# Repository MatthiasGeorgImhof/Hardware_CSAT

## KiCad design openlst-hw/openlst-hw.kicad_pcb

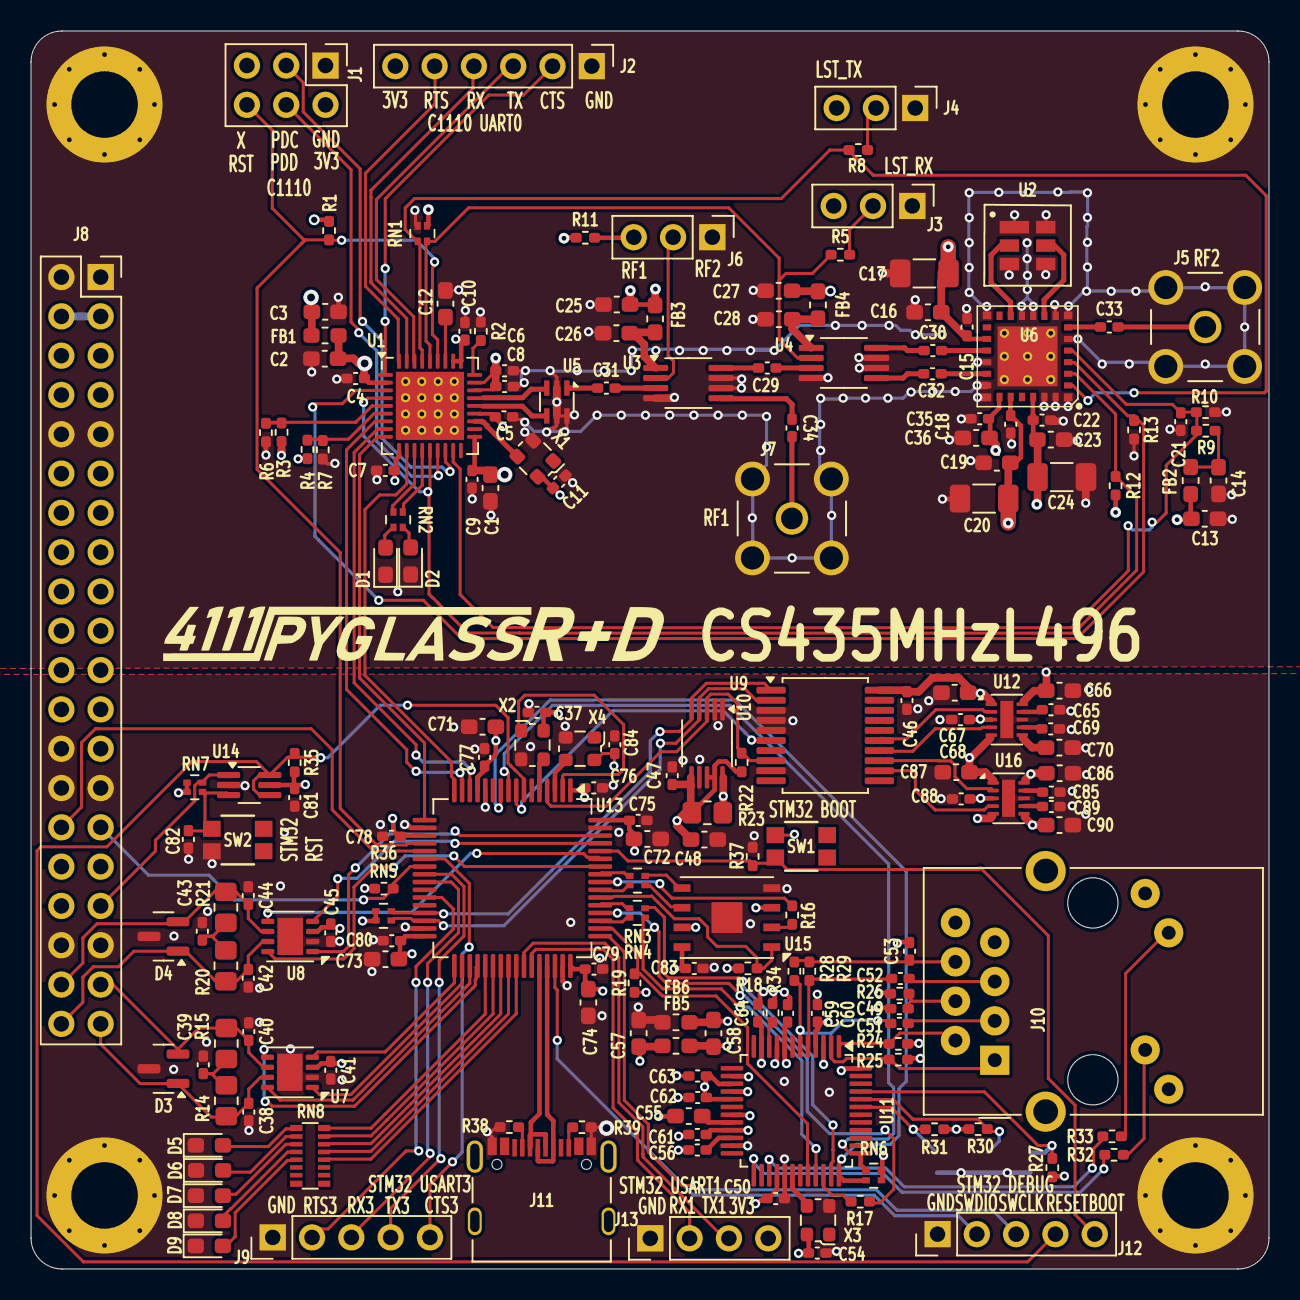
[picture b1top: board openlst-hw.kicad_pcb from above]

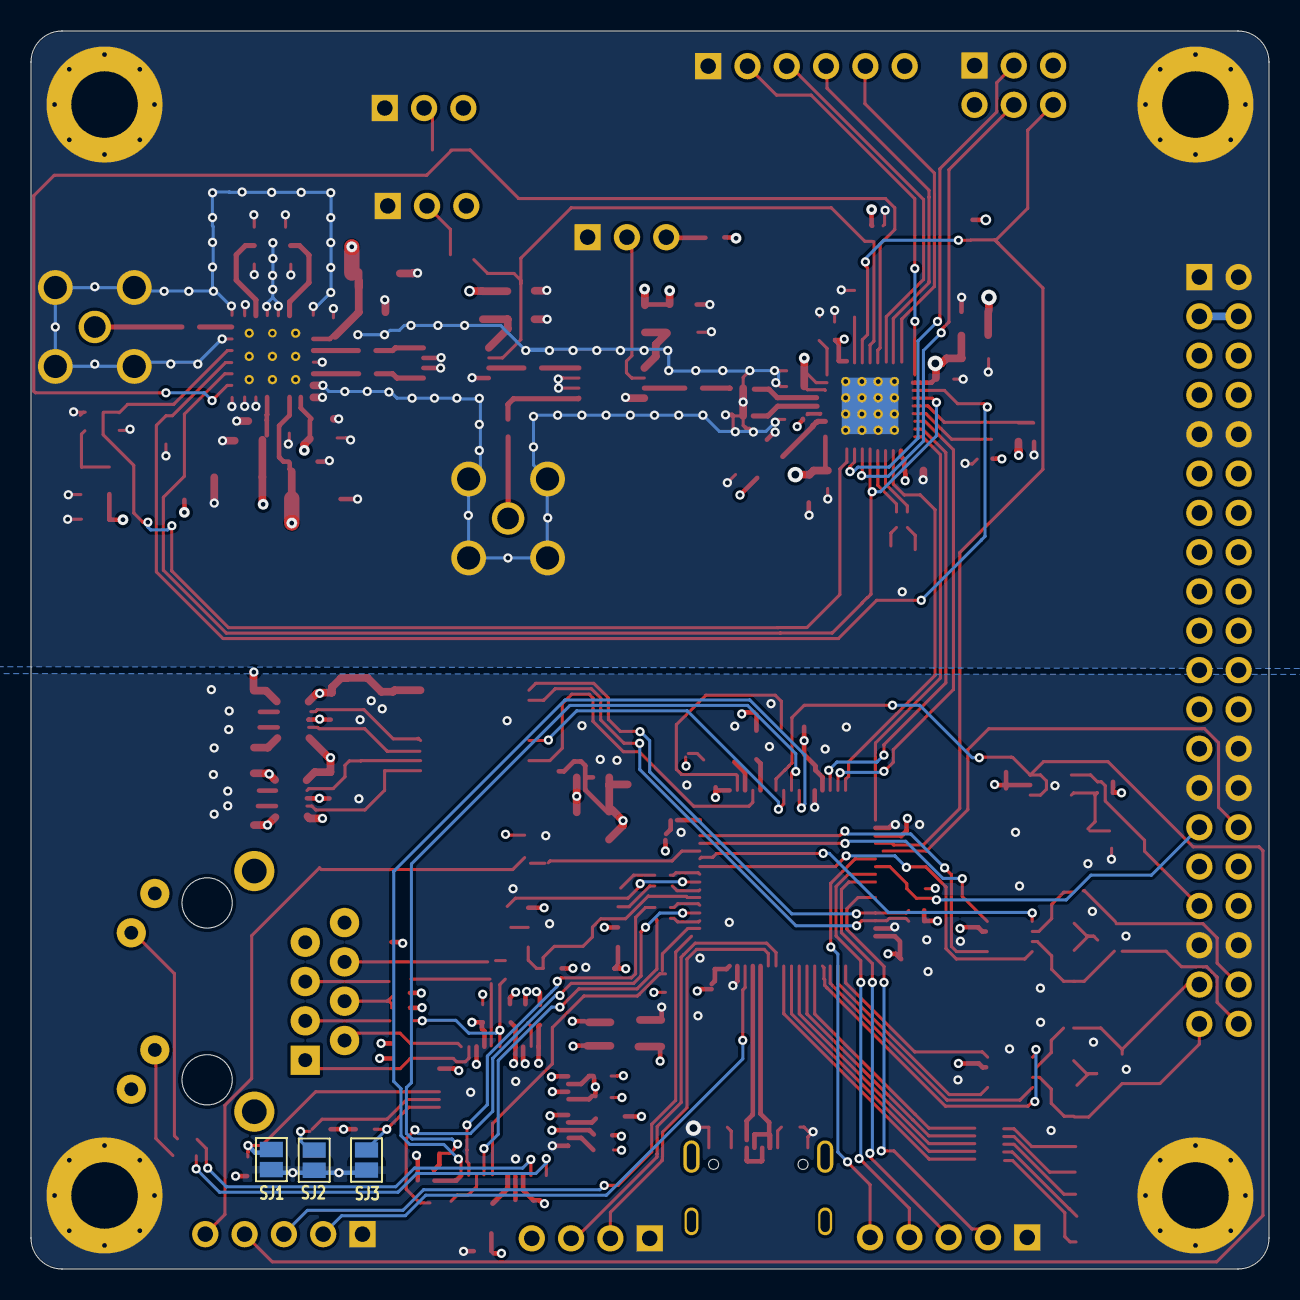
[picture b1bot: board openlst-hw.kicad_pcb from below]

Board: 4 copper layers, 80.0 x 80.0 mm, 194 parts (3 on the bottom side), 153 nets.

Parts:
C1, C16, C19, C23, C36, C48, C55, C57, C58, C66, C70, C71, C72, C73, C74, C86, C90: 10uF; C_0603_1608Metric_Pad1.08x0.95mm_HandSolder
C2, C3, C12, C13, C14, C25, C26, C27, C28: 1uF; C_0603_1608Metric_Pad1.08x0.95mm_HandSolder
C4, C5, C6, C7, C8, C9, C10, C11, C15, C18, C21, C22, C35, C37, C41, C45, C46, C47, C50, C54, C56, C59, C60, C61, C62, C63, C64, C68, C75, C76, C77, C78, C79, C80, C81, C82, C83, C84, C88: 100nF; C_0402_1005Metric_Pad0.74x0.62mm_HandSolder
C17, C20, C24: 47uF; C_1206_3216Metric_Pad1.33x1.80mm_HandSolder
C29, C30, C31, C32, C33, C34, C65, C69, C85, C89: 220pF; C_0402_1005Metric_Pad0.74x0.62mm_HandSolder
C38, C40, C42, C44: 100pF; C_0402_1005Metric_Pad0.74x0.62mm_HandSolder
C39, C43: 4nF7; C_0402_1005Metric_Pad0.74x0.62mm_HandSolder
C49, C53: 10nF; C_0402_1005Metric_Pad0.74x0.62mm_HandSolder
C51, C52: 6.8nF; C_0402_1005Metric_Pad0.74x0.62mm_HandSolder
C67, C87: 22uF; C_0603_1608Metric_Pad1.08x0.95mm_HandSolder
D1, D6: GREEN; LED_0603_1608Metric_Pad1.05x0.95mm_HandSolder
D2, D7, D8, D9: YELLOW; LED_0603_1608Metric_Pad1.05x0.95mm_HandSolder
D3, D4: NUP2105LT1G; SOT-23
D5: RED; LED_0603_1608Metric_Pad1.05x0.95mm_HandSolder
FB1, FB2, FB3, FB4, FB5, FB6: 1K; L_0603_1608Metric_Pad1.05x0.95mm_HandSolder
H1, H2, H3, H4: MountingHole_Pad; MountingHole_4.3mm_M4_Pad_Via_Custom
J1: Conn_02x03_Pin; PinHeader_2x03_P2.54mm_Vertical
J2: Conn_01x06_Pin; PinHeader_1x06_P2.54mm_Vertical
J3, J4, J6: Conn_01x03_Pin; PinHeader_1x03_P2.54mm_Vertical
J5, J7: SMA Jack; LINX_CONSMA001-G
J8: PC104 Conn_02x20_Odd_Even; PinSocket_2x20_P2.54mm_Vertical
J9: Conn_01x05_Pin; PinHeader_1x05_P2.54mm_Vertical
J10: RJ45_Amphenol_RJMG1BD3B8K1ANR
J11: 10155435-00011LF; AMPHENOL_10155435-00011LF
J12: Conn_01x05_Pin Vertical; PinHeader_1x05_P2.54mm_Vertical
J13: Conn_01x04_Pin Vertical; PinHeader_1x04_P2.54mm_Vertical
R1, R18, R19, R22, R35, R37: 100K; R_0402_1005Metric_Pad0.72x0.64mm_HandSolder
R2: 56K; R_0402_1005Metric_Pad0.72x0.64mm_HandSolder
R3, R4, R11: 20K; R_0402_1005Metric_Pad0.72x0.64mm_HandSolder
R5, R8: 22; R_0402_1005Metric_Pad0.72x0.64mm_HandSolder
R6, R7: 47K; R_0402_1005Metric_Pad0.72x0.64mm_HandSolder
R9: 3K09; R_0402_1005Metric_Pad0.72x0.64mm_HandSolder
R10: 6K65; R_0402_1005Metric_Pad0.72x0.64mm_HandSolder
R12, R13: 1K; R_0402_1005Metric_Pad0.72x0.64mm_HandSolder
R14, R15, R20, R21: 60R4; R_0805_2012Metric_Pad1.20x1.40mm_HandSolder
R16, R17: 22R; R_0402_1005Metric_Pad0.72x0.64mm_HandSolder
R23: 10m; R_0805_2012Metric_Pad1.20x1.40mm_HandSolder
R24, R25, R28, R29: 49R9; R_0402_1005Metric_Pad0.72x0.64mm_HandSolder
R26: 10R; R_0402_1005Metric_Pad0.72x0.64mm_HandSolder
R27, R30, R31: 10K; R_0402_1005Metric_Pad0.72x0.64mm_HandSolder
R32, R33: 470R; R_0402_1005Metric_Pad0.72x0.64mm_HandSolder
R34: 12K4; R_0402_1005Metric_Pad0.72x0.64mm_HandSolder
R36: 330K; R_0402_1005Metric_Pad0.72x0.64mm_HandSolder
R38, R39: 5K1; R_0402_1005Metric_Pad0.72x0.64mm_HandSolder
RN1, RN6: 10K; R_Array_Convex_2x0402_widepads
RN2: 1K; R_Array_Convex_2x0402_widepads
RN3, RN4: 22R; R_Array_Convex_2x0402_widepads
RN5: 5K6; R_Array_Convex_2x0402_widepads
RN7: 100K; R_Array_Convex_2x0402_widepads
RN8: 1K; R_Array_Convex_8x0602_widepads
SJ1, SJ2, SJ3: SOLDERJUMPERREFLOW_NOPASTE; SolderJumper-2_P1.3mm_Open_Pad1.0x1.5mm
SW1, SW2: EVP-AA602W; EVP602AA
U1: CC1110; Texas_RHH0036C_VQFN-36-1EP_6x6mm_P0.5mm_EP4.4x4.4mm_Thermal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
U2: TA1808A; SF2446E
U3, U4: PE4250MLI; MSOP-8_3x3mm_P0.65mm
U5: 0433BM15A0001; Balun_Johanson_0896BM15A0001
U6: RFFM6406
U7, U8: TCAN3414; VSON-8-1EP_3x3mm_P0.65mm_EP1.65x2.4mm
U9: MCP23008T-E/SS; SSOP-20_5.3x7.2mm_P0.65mm
U10: INA226AIDGSR; VSSOP-10_3x3mm_P0.5mm
U11: W5500; LQFP-48_7x7mm_P0.5mm
U12, U16: TPS22968QDMGRQ1; WSON-10-1EP_2x3mm_P0.5mm_EP0.84x2.4mm
U13: STM32L496RGTx; LQFP-64_10x10mm_P0.5mm
U14: 74LVC2G07; SOT-363_SC-70-6_Handsoldering
U15: MR25H10; DFN-8-1EP_6x5mm_P1.27mm_EP2x2mm
X1: 27MHz; Oscillator_SMD_ECS_2520MV-xxx-xx-4Pin_2.5x2.0mm
X2: 10MHz; Oscillator_SMD_ECS_2520MV-xxx-xx-4Pin_2.5x2.0mm
X3: 25MHz; Oscillator_SMD_ECS_2520MV-xxx-xx-4Pin_2.5x2.0mm
X4: 32.768KHZ; Oscillator_SMD_ECS_2520MV-xxx-xx-4Pin_2.5x2.0mm

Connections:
/3V3_AUX: J8.15, R23.1, U10.10 (IN+)
/3V3_BRIDGE: C37.1, C41.1, C45.1, C71.1, C72.1, C73.1, C74.1, C75.1, C76.1, C77.1, C78.1, C79.1, C80.1, C81.2, C84.1, J8.16, J13.4, R35.1, R36.1, RN5.3 (R2.2), RN5.4 (R1.2), RN7.1 (R1.1), RN7.2 (R2.1), SW1.1, U7.3 (VCC), U8.3 (VCC), U13.1 (VBAT), U13.13 (VDDA), U13.19 (VDD), U13.32 (VDD), U13.48 (VDDUSB), U13.64 (VDD), U14.5 (VCC), X2.4 (VDD), X4.4 (VCC)
/3V3_COMM: C3.1, C11.1, C13.1, C25.1, C27.1, C35.1, C36.1, C66.1, FB1.1, FB2.2, FB3.2, FB4.2, J1.2, J2.6, J3.3, J4.3, R1.2, R3.2, R11.1, R12.2, RN1.3 (R2.2), U6.23 (VDD), U12.10 (VOUT1), X1.4 (Vcc)
/3V3_LAN: C50.1, C54.1, C57.1, C90.2, FB5.1, J10.L1, J10.L4, R19.1, R27.1, R30.1, R31.1, RN6.3 (R2.2), RN6.4 (R1.2), U11.28 (VDD), U16.6 (VOUT2), X3.4 (VCC)
/CAN Bridge/3V3_MRAM: C83.1, C86.1, R18.1, U15.3 (~WP), U15.7 (~HOLD), U15.8 (VDD), U16.10 (VOUT1)
/CAN Bridge/ATTENTION: J8.29, R36.2, U13.23 (PA7)
/CAN Bridge/CAN1_H: C42.1, D4.1 (K), J8.40, R20.1, U8.7 (CANH)
/CAN Bridge/CAN1_L: C44.2, D4.2 (K), J8.38, R21.2, U8.6 (CANL)
/CAN Bridge/CAN2_H: C38.1, D3.1 (K), J8.39, R14.1, U7.7 (CANH)
/CAN Bridge/CAN2_L: C40.2, D3.2 (K), J8.37, R15.2, U7.6 (CANL)
/CAN Bridge/CAN Transceiver1/CAN_RX: U8.4 (RXD), U13.61 (PB8)
/CAN Bridge/CAN Transceiver1/CAN_TX: U8.1 (TXD), U13.62 (PB9)
/CAN Bridge/CAN Transceiver1/SHDN: U8.5 (SHTD), U13.59 (PB7)
/CAN Bridge/CAN Transceiver1/STB: U8.8 (STB), U13.58 (PB6)
/CAN Bridge/CAN Transceiver2/CAN_RX: U7.4 (RXD), U13.33 (PB12)
/CAN Bridge/CAN Transceiver2/CAN_TX: U7.1 (TXD), U13.34 (PB13)
/CAN Bridge/CAN Transceiver2/SHDN: U7.5 (SHTD), U13.36 (PB15)
/CAN Bridge/CAN Transceiver2/STB: U7.8 (STB), U13.35 (PB14)
/CAN Bridge/COMM1_RST: J8.33, RN7.4 (R1.2), U14.1 (IN1)
/CAN Bridge/EPS_RST: J8.30, U13.21 (PA5)
/CAN Bridge/I2C2_SCL: RN5.2 (R2.1), U9.1 (SCL), U10.5 (SCL), U13.29 (PB10)
/CAN Bridge/I2C2_SDA: RN5.1 (R1.1), U9.2 (SDA), U10.4 (SDA), U13.30 (PB11)
/CAN Bridge/MRAM/SPI_MISO: R16.1, U15.2 (SO)
/CAN Bridge/MRAM/SPI_MOSI: RN3.2 (R2.1), U15.5 (SI)
/CAN Bridge/MRAM/SPI_SCK: RN3.1 (R1.1), U15.6 (SCK)
/CAN Bridge/PMIC/BOOT: J12.5, R37.1, SW1.2, U13.60 (PH3_BOOT0)
/CAN Bridge/PMIC/EXTI2_LAN: RN6.2 (R2.1), U11.36 (~INT), U13.10 (PC2)
/CAN Bridge/PMIC/HSE_EN: U13.2 (PC13), X2.1 (TRI-STATE)
/CAN Bridge/PMIC/HSE_IN: U13.5 (PH0), X2.3 (OUTPUT)
/CAN Bridge/PMIC/LAN_RST: RN6.1 (R1.1), U11.37 (~RST), U13.9 (PC1)
/CAN Bridge/PMIC/LED1: RN8.16 (R), U13.37 (PC6)
/CAN Bridge/PMIC/LED2: RN8.15 (R), U13.38 (PC7)
/CAN Bridge/PMIC/LED3: RN8.14 (R), U13.39 (PC8)
/CAN Bridge/PMIC/LED4: RN8.13 (R), U13.40 (PC9)
/CAN Bridge/PMIC/LED5: RN8.12 (R), U13.41 (PA8)
/CAN Bridge/PMIC/NRST: J12.4, R35.2, U13.7 (NRST), U14.4 (OUT2), U14.6 (OUT1)
/CAN Bridge/PMIC/OSC32_IN: U13.3 (PC14), X4.3 (OUT)
/CAN Bridge/PMIC/RESET: C82.1, RN7.3 (R2.2), SW2.3, U14.3 (IN2)
/CAN Bridge/PMIC/SPI1_MISO: R16.2, U13.56 (PB4)
/CAN Bridge/PMIC/SPI1_MOSI: RN3.3 (R2.2), U13.57 (PB5)
/CAN Bridge/PMIC/SPI1_SCK: RN3.4 (R1.2), U13.55 (PB3)
/CAN Bridge/PMIC/SPI3_MISO: R17.1, U13.52 (PC11)
/CAN Bridge/PMIC/SPI3_MOSI: RN4.3 (R2.2), U13.53 (PC12)
/CAN Bridge/PMIC/SPI3_SCK: RN4.4 (R1.2), U13.51 (PC10)
/CAN Bridge/PMIC/SYS_JTMS_SWCLK: J12.3, U13.49 (PA14)
/CAN Bridge/PMIC/SYS_JTMS_SWDIO: J12.2, U13.46 (PA13)
/CAN Bridge/PMIC/USART1_RX: J13.2, U13.43 (PA10)
/CAN Bridge/PMIC/USART1_TX: J13.3, U13.42 (PA9)
/CAN Bridge/PMIC/USART3_CTS: J9.5, U13.22 (PA6)
/CAN Bridge/PMIC/USART3_RTS: J9.2, U13.27 (PB1)
/CAN Bridge/PMIC/USART3_RX: J9.3, U13.25 (PC5)
/CAN Bridge/PMIC/USART3_TX: J9.4, U13.24 (PC4)
/CAN Bridge/PMIC/USB/DN: J11.A7 (DN1_A), J11.B7 (DN2_B), U13.44 (PA11)
/CAN Bridge/PMIC/USB/DP: J11.A6 (DP1_A), J11.B6 (DP2_B), U13.45 (PA12)
/CAN Bridge/Power Switch/ENABLE0: U9.12 (GP0), U16.4 (ON2)
/CAN Bridge/Power Switch/ENABLE1: U9.13 (GP1), U16.2 (ON1)
/CAN Bridge/Power Switch/ENABLE2: U9.14 (GP2), U12.4 (ON2)
/CAN Bridge/Power Switch/ENABLE3: U9.15 (GP3), U12.2 (ON1)
/CAN Bridge/Power Switch/VBUS: C46.1, C47.1, C48.1, C67.1, C68.1, C87.1, C88.1, R22.1, R23.2, U9.20 (VDD), U10.6 (VS), U10.8 (VBUS), U10.9 (IN-), U12.1 (VIN1), U12.3 (VBIAS), U12.5 (VIN2), U16.1 (VIN1), U16.3 (VBIAS), U16.5 (VIN2)
/CAN Bridge/Power Switch/VOUT2: C70.2, U12.6 (VOUT2)
/CAN Bridge/Power_INT: R22.2, U9.8 (INT), U10.3 (ALERT), U13.4 (PC15)
/CAN Bridge/Power_RST: U9.6 (*RESET), U13.8 (PC0)
/CAN Bridge/SPI1_CS_LAN: R19.2, U11.32 (~SCS), U13.50 (PA15)
/CAN Bridge/SPI1_CS_MRAM: R18.2, U13.54 (PD2), U15.1 (~CS)
/CAN Bridge/SPI_LAN/AGND: C49.2, C53.2, C55.2, C56.2, C58.2, C59.2, C60.2, C61.2, C62.2, C63.2, C64.2, FB6.2, J10.R8, R34.2, U11.3 (AGND), U11.9 (AGND), U11.14 (AGND), U11.16 (AGND), U11.19 (AGND), U11.48 (AGND)
/CAN Bridge/SPI_LAN/AVDD: C58.1, C59.1, C60.1, C61.1, C62.1, C63.1, C64.1, FB5.2, R24.1, R25.1, R26.1, U11.4 (AVDD), U11.8 (AVDD), U11.11 (AVDD), U11.15 (AVDD), U11.17 (AVDD), U11.21 (AVDD)
/CAN Bridge/SPI_LAN/GREENLED: J10.L3, R32.1
/CAN Bridge/SPI_LAN/MISO: R17.2, U11.34 (MISO)
/CAN Bridge/SPI_LAN/MOSI: RN4.2 (R2.1), U11.35 (MOSI)
/CAN Bridge/SPI_LAN/RX+: C51.2, R28.2, U11.6 (RXP)
/CAN Bridge/SPI_LAN/RX-: C52.2, R29.2, U11.5 (RXN)
/CAN Bridge/SPI_LAN/SCKL: RN4.1 (R1.1), U11.33 (SCLK)
/CAN Bridge/SPI_LAN/TX+: J10.R1 (TD+), R25.2, U11.2 (TXP)
/CAN Bridge/SPI_LAN/TX-: J10.R2 (TD-), R24.2, U11.1 (TXN)
/CAN Bridge/SPI_LAN/YELLOWLED: J10.L2, R33.1
/CAN Bridge/UART_CTS: U1.8 (P0_3), U13.14 (PA0)
/CAN Bridge/UART_RTS: U1.7 (P0_2), U13.15 (PA1)
/CAN Bridge/UART_RX: U1.9 (P0_4), U13.17 (PA3)
/CAN Bridge/UART_TX: U1.11 (P0_5), U13.16 (PA2)
/GND: C1.2, C2.2, C3.2, C4.2, C5.2, C6.2, C7.2, C8.2, C9.2, C10.2, C11.2, C12.2, C13.2, C14.2, C15.2, C16.2, C17.2, C18.2, C19.2, C20.2, C21.2, C22.2, C23.2, C24.2, C25.2, C26.2, C27.2, C28.2, C35.2, C36.2, C37.2, C38.2, C39.2, C40.1, C41.2, C42.2, C43.2, C44.1, C45.2, C46.2, C47.2, C48.2, C50.2, C54.2, C57.2, C65.2, C66.2, C67.2, C68.2, C69.1, C70.1, C71.2, C72.2, C73.2, C74.2, C75.2, C76.2, C77.2, C78.2, C79.2, C80.2, C81.1, C82.2, C83.2, C84.2, C85.2, C86.2, C87.2, C88.2, C89.1, C90.1, D1.1 (K), D2.1 (K), D3.3 (A), D4.3 (A), D5.1 (K), D6.1 (K), D7.1 (K), D8.1 (K), D9.1 (K), FB6.1, H1.1, H2.1, H3.1, H4.1, J1.1, J2.1, J3.1, J4.1, J5.2 (Ext), J6.1, J7.2 (Ext), J8.1, J8.2, J8.9, J8.10, J8.26, J8.27, J8.28, J8.35, J8.36, J9.1, J11.A1_B12 (GND), J11.B1_A12 (GND__1), J12.1, J13.1, R2.1, R6.1, R7.1, R10.2, R13.1, R37.2, R38.1, R39.1, RN1.4 (R1.2), SJ1.2 (B), SJ2.2 (B), SJ3.2 (B), SW2.4, U1.37 (GND_PAD), U2.1 (GND), U2.3 (GND), U2.4 (GND), U2.6 (GND), U3.4 (GND), U3.6 (GND), U3.7 (GND), U4.4 (GND), U4.6 (GND), U4.7 (GND), U5.2 (GND), U5.5 (GND), U5.6 (GND), U6.1 (GND), U6.6 (GND), U6.8 (GND), U6.9 (GND), U6.11 (GND), U6.12 (GND), U6.15 (GND), U6.19 (GND), U6.21 (GND), U6.22 (GND), U6.27 (GND), U6.28 (GND), U6.29 (PAD), U7.2 (GND), U7.9 (GND), U8.2 (GND), U8.9 (GND), U9.3 (A2), U9.4 (A1), U9.5 (A0), U9.9 (VSS), U10.1 (A1), U10.2 (A0), U10.7 (GND), U11.23 (RSVD), U11.29 (GND), U12.8 (GND), U12.11 (TPAD), U13.12 (VSSA), U13.18 (VSS), U13.31 (VSS), U13.47 (VSS), U13.63 (VSS), U14.2 (GND), U15.4 (VSS), U15.9 (PAD), U16.8 (GND), U16.11 (TPAD), X1.2 (GND), X2.2 (GND), X3.2 (GND), X4.2 (GND)
/INTERBOARD_CONNECTOR2/BATT: J8.3, J8.4
/MCU/+3V3_C1110: C1.1, C2.1, C4.1, C5.1, C6.1, C7.1, C8.1, C9.1, C10.1, FB1.2, U1.2 (DVDD), U1.10 (DVDD), U1.19 (AVDD), U1.22 (AVDD), U1.25 (AVDD), U1.26 (AVDD), U1.28 (GUARD), U1.29 (AVDD_DREG)
/MCU/AN0: R3.1, R6.2, U1.5 (P0_0)
/MCU/AN1: R4.1, R7.2, U1.6 (P0_1)
/MCU/LED1: RN2.2 (R2.1), U1.12 (P0_6)
/MCU/LED2: RN2.1 (R1.1), U1.13 (P0_7)
/MCU/LST_RX_MODE: R5.1, RN1.2 (R2.1), U1.32 (P1_7), U4.2 (V1)
/MCU/LST_TX_MODE: R8.1, RN1.1 (R1.1), U1.33 (P1_6), U6.2 (TR)
/MCU/PA_VAPC: C21.1, R9.2, R10.1, U1.17 (P2_3/XOSC32-1), U6.5 (VAPC)
/MCU/RF_BYP: R13.2, U1.3 (P1_1), U6.4 (BYP)
/MCU/RF_EN: R12.1, U1.4 (P1_0), U1.14 (P2_0), U6.3 (EN)
/MCU/RF_N: U1.24 (RF_N), U5.3
/MCU/RF_P: U1.23 (RF_P), U5.4
/MCU/UART0_CTS: J2.2, U1.1 (P1_2)
/MCU/UART0_RTS: J2.5, U1.36 (P1_3)
/MCU/UART0_RX: J2.4, U1.35 (P1_4)
/MCU/UART0_TX: J2.3, U1.34 (P1_5)
/VRF: C15.1, C16.1, C17.1, C18.1, C19.1, C20.1, C22.1, C23.1, C24.1, J8.5, R4.2, U6.17 (VCC_RX), U6.24 (VCC_TX1), U6.26 (VCC_TX2)
LST_RESET: J1.6, R1.1, U1.31 (RESET_N), U13.20 (PA4)
unnamed: C14.1, FB2.1, R9.1
unnamed: C31.1, U5.1
unnamed: C39.1, R14.2, R15.1
unnamed: C43.1, R20.2, R21.1
unnamed: D1.2 (A), RN2.3 (R2.2)
unnamed: D2.2 (A), RN2.4 (R1.2)
unnamed: D5.2 (A), RN8.1 (R)
unnamed: D6.2 (A), RN8.2 (R)
unnamed: D7.2 (A), RN8.3 (R)
unnamed: D8.2 (A), RN8.4 (R)
unnamed: D9.2 (A), RN8.5 (R)
unnamed: J3.2, R5.2
unnamed: J4.2, R8.2
unnamed: C33.2, J5.1 (In)
unnamed: J6.2, U3.2 (V1)
unnamed: J6.3, R11.2
unnamed: C34.2, J7.1 (In)
unnamed: C52.1, J10.R5 (RCT)
unnamed: C51.1, J10.R3 (RD+)
unnamed: C53.1, J10.R6 (RD-), R28.1, R29.1
unnamed: C49.1, J10.R4 (TCT), R26.2
unnamed: J11.A5 (CC1_A), R38.2
unnamed: J11.B5 (CC2_B), R39.2
unnamed: R27.2, SJ1.1 (A), U11.45 (PMODE0)
unnamed: R30.2, SJ2.1 (A), U11.44 (PMODE1)
unnamed: R31.2, SJ3.1 (A), U11.43 (PMODE2)
unnamed: C12.1, U1.30 (DCOUPL)
unnamed: R2.2, U1.27 (RBIAS)
unnamed: U1.21 (XOSC-1), X1.3 (OUT)
unnamed: C34.1, U3.5 (RF1)
unnamed: C29.1, U3.8 (RF2)
unnamed: C31.2, U3.3 (RFC)
unnamed: C26.1, FB3.1, U3.1 (V2)
unnamed: C32.1, U4.5 (RF1)
unnamed: C30.1, U4.8 (RF2)
unnamed: C29.2, U4.3 (RFC)
unnamed: C28.1, FB4.1, U4.1 (V2)
unnamed: C33.1, U6.7 (ANT)
unnamed: C30.2, U6.18 (RX)
unnamed: U2.5 (RF), U6.10 (SAW1)
unnamed: U2.2 (RF), U6.13 (SAW2)
unnamed: C32.2, U6.20 (TX)
unnamed: C56.1, U11.22 (1V2O)
unnamed: R33.2, U11.27 (ACTLED)
unnamed: R34.1, U11.10 (EXRES1)
unnamed: R32.2, U11.25 (LINKLED)
unnamed: C55.1, U11.20 (TOCAP)
unnamed: U11.30 (XI/CLKIN), X3.3 (OUT)
unnamed: C65.1, U12.9 (CT1)
unnamed: C69.2, U12.7 (CT2)
unnamed: C85.1, U16.9 (CT1)
unnamed: C89.2, U16.7 (CT2)
PROG_DC: J1.3, U1.16 (P2_2)
PROG_DD: J1.4, U1.15 (P2_1)

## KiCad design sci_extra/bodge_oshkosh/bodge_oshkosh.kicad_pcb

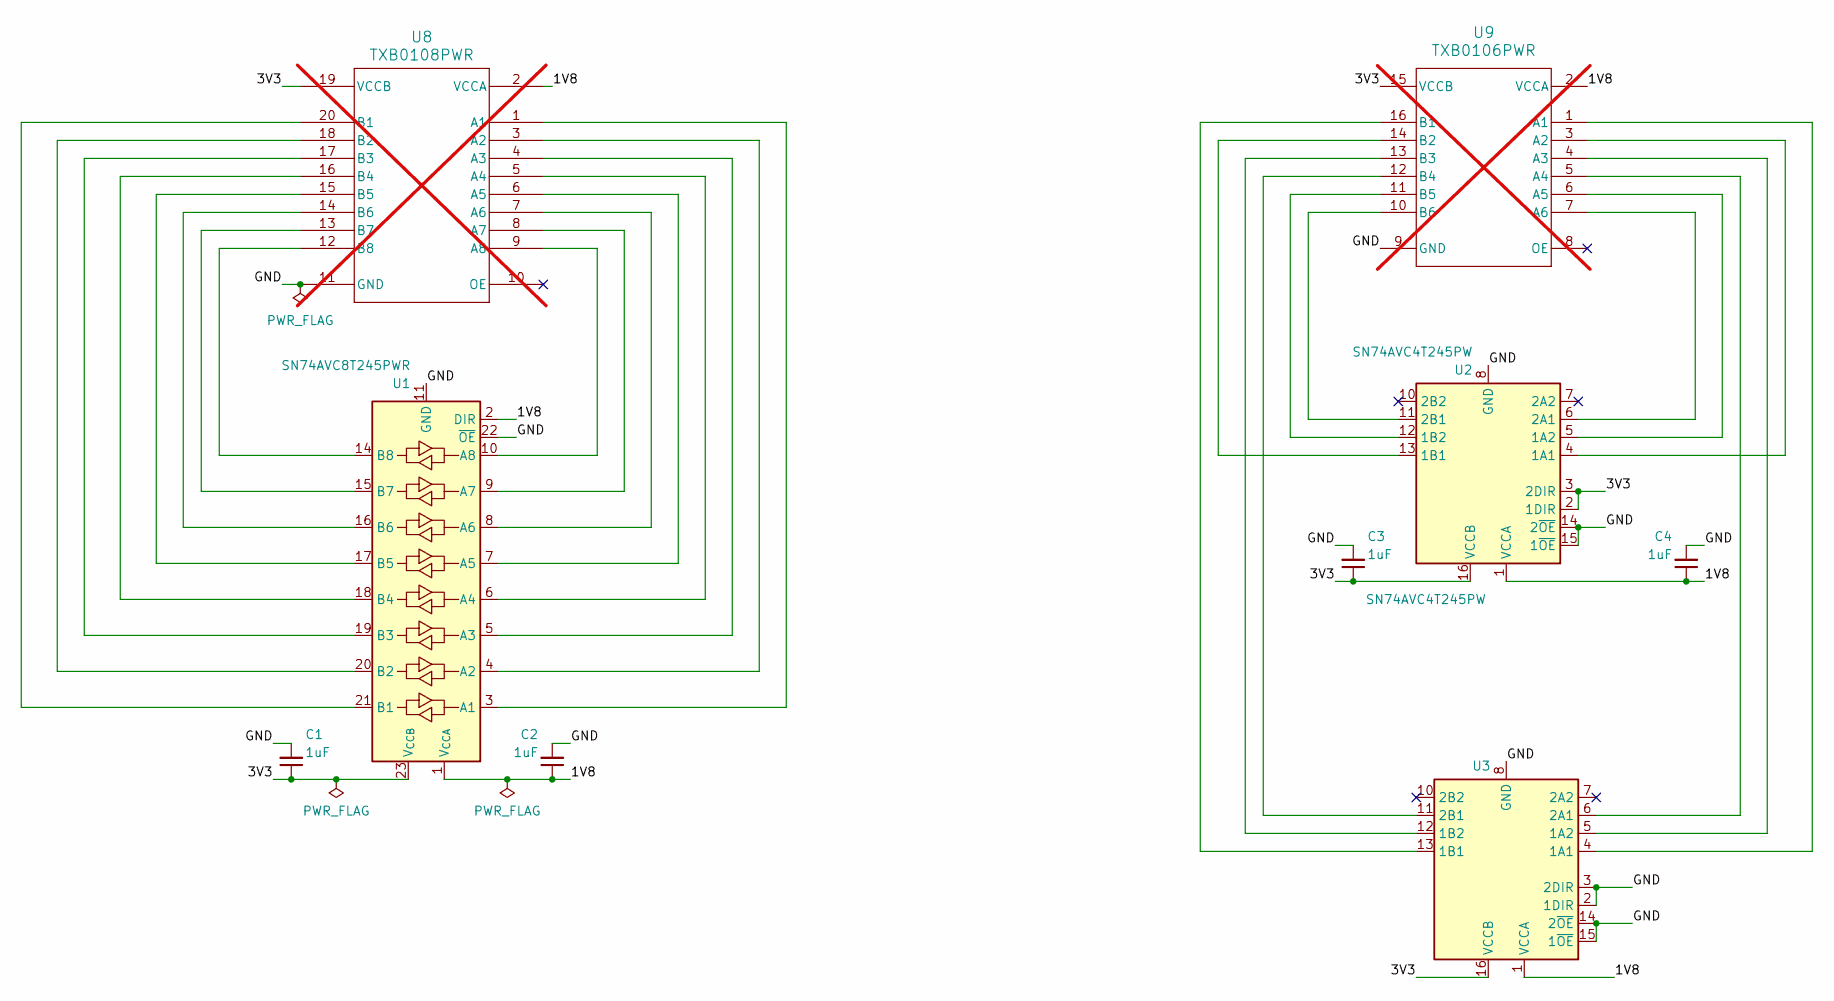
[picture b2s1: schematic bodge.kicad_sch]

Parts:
C1, C2, C3, C4: 1uF; C_0402_1005Metric_Pad0.74x0.62mm_HandSolder; Tolerance 10; Voltage 25; Part Number GRM155R61C105MA12D
U1: SN74AVC8T245PWR; TSSOP-24_4.4x7.8mm_P0.65mm; Part Number SN74AVC8T245PWR
U2, U3: SN74AVC4T245PW; TSSOP-16_4.4x5mm_P0.65mm; Part Number SN74AVC4T245PW
U8: TXB0108PWR; TSSOP-20_4.4x6.5mm_P0.65mm_Flipped; Part Number TXB0108PWR; not fitted
U9: TXB0106PWR; TSSOP-16_4.4x5mm_P0.65mm_Flipped; Part Number TXB0106PWR; not fitted

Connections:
/1V8: C2.1, C4.1, U1.1 (V_{CCA}), U1.2 (DIR), U2.1 (VCCA), U3.1 (VCCA), U8.2 (VCCA), U9.2 (VCCA)
/3V3: C1.1, C3.1, U1.23 (V_{CCB}), U1.24 (V_{CCB}), U2.2 (1DIR), U2.3 (2DIR), U2.16 (VCCB), U3.16 (VCCB), U8.19 (VCCB), U9.15 (VCCB)
/GND: C1.2, C2.2, C3.2, C4.2, U1.11 (GND), U1.12 (GND), U1.13 (GND), U1.22 (~OE), U2.8 (GND), U2.9 (GND), U2.14 (2~OE), U2.15 (1~OE), U3.2 (1DIR), U3.3 (2DIR), U3.8 (GND), U3.9 (GND), U3.14 (2~OE), U3.15 (1~OE), U8.11 (GND), U9.9 (GND)
unnamed: U1.3 (A1), U8.1 (A1)
unnamed: U1.4 (A2), U8.3 (A2)
unnamed: U1.5 (A3), U8.4 (A3)
unnamed: U1.6 (A4), U8.5 (A4)
unnamed: U1.7 (A5), U8.6 (A5)
unnamed: U1.8 (A6), U8.7 (A6)
unnamed: U1.9 (A7), U8.8 (A7)
unnamed: U1.10 (A8), U8.9 (A8)
unnamed: U1.21 (B1), U8.20 (B1)
unnamed: U1.20 (B2), U8.18 (B2)
unnamed: U1.19 (B3), U8.17 (B3)
unnamed: U1.18 (B4), U8.16 (B4)
unnamed: U1.17 (B5), U8.15 (B5)
unnamed: U1.16 (B6), U8.14 (B6)
unnamed: U1.15 (B7), U8.13 (B7)
unnamed: U1.14 (B8), U8.12 (B8)
unnamed: U2.4 (1A1), U9.3 (A2)
unnamed: U2.5 (1A2), U9.6 (A5)
unnamed: U2.13 (1B1), U9.14 (B2)
unnamed: U2.12 (1B2), U9.11 (B5)
unnamed: U2.6 (2A1), U9.7 (A6)
unnamed: U2.11 (2B1), U9.10 (B6)
unnamed: U3.4 (1A1), U9.1 (A1)
unnamed: U3.5 (1A2), U9.4 (A3)
unnamed: U3.13 (1B1), U9.16 (B1)
unnamed: U3.12 (1B2), U9.13 (B3)
unnamed: U3.6 (2A1), U9.5 (A4)
unnamed: U3.11 (2B1), U9.12 (B4)

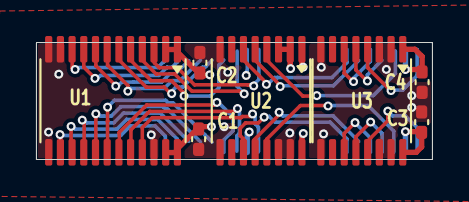
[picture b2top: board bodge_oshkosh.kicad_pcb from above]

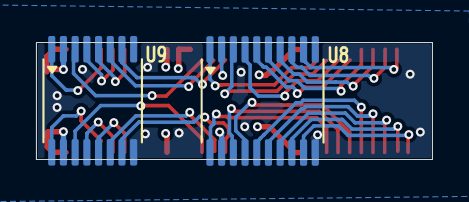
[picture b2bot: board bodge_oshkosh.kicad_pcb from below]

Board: 4 copper layers, 22.0 x 6.5 mm, 9 parts (2 on the bottom side), 31 nets.
